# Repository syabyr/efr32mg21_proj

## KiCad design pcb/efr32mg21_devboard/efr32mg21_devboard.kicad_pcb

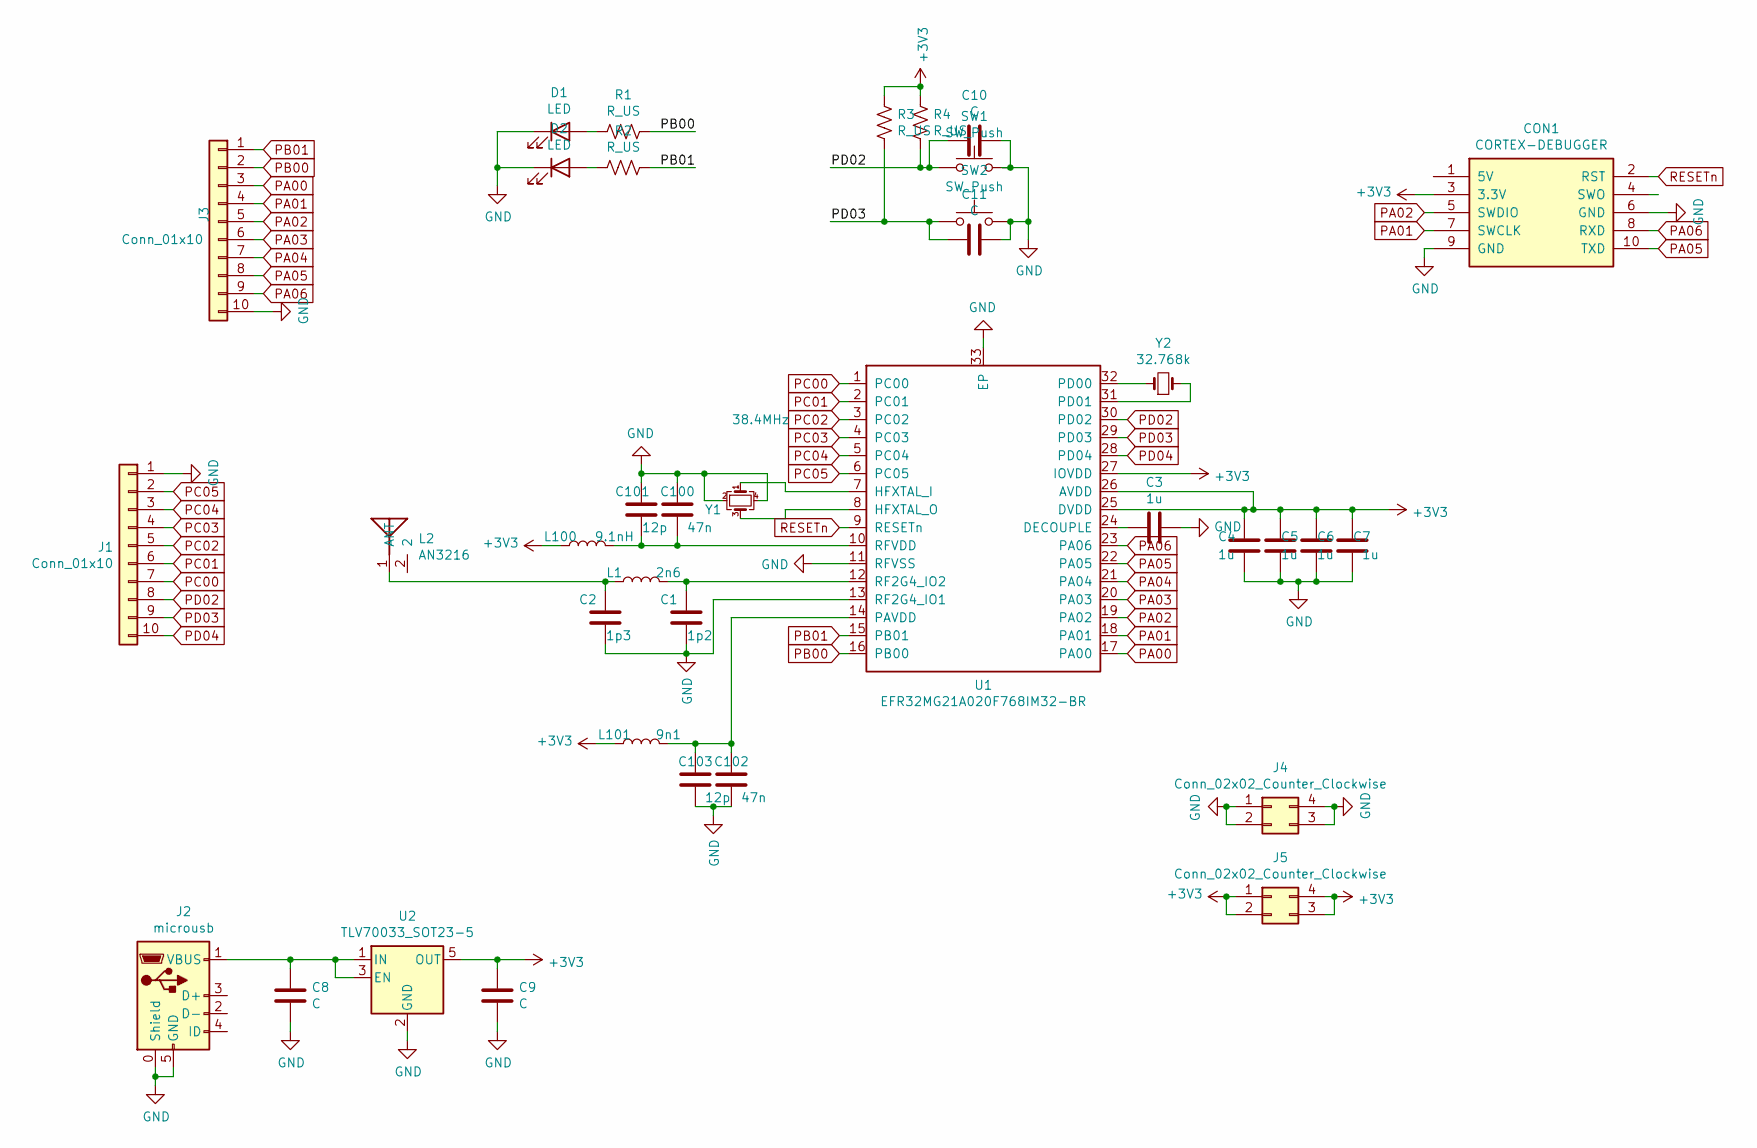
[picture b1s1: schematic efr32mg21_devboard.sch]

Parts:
C1: 1p2; C_0402_1005Metric
C2: 1p3; C_0402_1005Metric
C3, C4, C5, C6, C7: 1u; C_0402_1005Metric
C8, C9: C; C_1206_3216Metric
C10, C11: C; C_0603_1608Metric_Pad1.08x0.95mm_HandSolder
C100, C102: 47n; C_0402_1005Metric
C101, C103: 12p; C_0402_1005Metric
CON1: CORTEX-DEBUGGER; debugger_2x05_P1.27mm_Vertical
D1, D2: LED; LED_0805_2012Metric
J1, J3: Conn_01x10; PinHeader_1x10_P2.54mm_Vertical
J2: microusb; MICRO-USB_MICRO-USB-17
J4, J5: Conn_02x02_Counter_Clockwise; PinHeader_2x02_P2.54mm_Vertical
L1: 2n6; L_0402_1005Metric
L2: AN3216; ANT3216-2.4G
L100: 9.1nH; L_0603_1608Metric
L101: 9n1; L_0603_1608Metric
R1, R2, R3, R4: R_US; R_0603_1608Metric_Pad0.98x0.95mm_HandSolder
SW1, SW2: SW_Push; turtlekey
U1: EFR32MG21A020F768IM32-BR; QFN-32-1EP_4x4mm_P0.4mm_EP2.9x2.9mm
U2: TLV70033_SOT23-5; SOT-23-5
Y1: 38.4MHz; Crystal_SMD_3225-4Pin_3.2x2.5mm
Y2: 32.768k; Crystal_SMD_3215-2Pin_3.2x1.5mm

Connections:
+3V3: C4.2, C5.2, C6.2, C7.2, C9.1, CON1.3 (3.3V), J5.1, J5.2, J5.3, J5.4, L100.1, L101.1, R3.2, R4.2, U1.25 (DVDD), U1.26 (AVDD), U1.27 (IOVDD), U2.5 (OUT)
GND: C1.1, C2.1, C3.1, C4.1, C5.1, C6.1, C7.1, C8.2, C9.2, C10.1, C11.1, C100.2, C101.2, C102.1, C103.1, CON1.6 (GND), CON1.9 (GND), D1.1 (K), D2.1 (K), J1.1, J2.0 (Shield), J2.5 (GND), J3.10, J4.1, J4.2, J4.3, J4.4, SW1.2, SW2.2, U1.11 (RFVSS), U1.13 (RF2G4_IO1), U1.33 (EP), U2.2 (GND), Y1.2, Y1.4
unnamed: C1.2, L1.2, U1.12 (RF2G4_IO2)
unnamed: C2.2, L1.1, L2.1 (ANT)
unnamed: C3.2, U1.24 (DECOUPLE)
unnamed: C8.1, J2.1 (VBUS), U2.1 (IN), U2.3 (EN)
unnamed: C100.1, C101.1, L100.2, U1.10 (RFVDD)
unnamed: C102.2, C103.2, L101.2, U1.14 (PAVDD)
unnamed: D1.2 (A), R1.2
unnamed: D2.2 (A), R2.2
unnamed: U1.7 (HFXTAL_I), Y1.1
unnamed: U1.8 (HFXTAL_O), Y1.3
unnamed: U1.31 (PD01), Y2.2
unnamed: U1.32 (PD00), Y2.1
PA00: J3.3, U1.17 (PA00)
PA01: CON1.7 (SWCLK), J3.4, U1.18 (PA01)
PA02: CON1.5 (SWDIO), J3.5, U1.19 (PA02)
PA03: J3.6, U1.20 (PA03)
PA04: J3.7, U1.21 (PA04)
PA05: CON1.10 (TXD), J3.8, U1.22 (PA05)
PA06: CON1.8 (RXD), J3.9, U1.23 (PA06)
PB00: J3.2, R1.1, U1.16 (PB00)
PB01: J3.1, R2.1, U1.15 (PB01)
PC00: J1.7, U1.1 (PC00)
PC01: J1.6, U1.2 (PC01)
PC02: J1.5, U1.3 (PC02)
PC03: J1.4, U1.4 (PC03)
PC04: J1.3, U1.5 (PC04)
PC05: J1.2, U1.6 (PC05)
PD02: C10.2, J1.8, R4.1, SW1.1, U1.30 (PD02)
PD03: C11.2, J1.9, R3.1, SW2.1, U1.29 (PD03)
PD04: J1.10, U1.28 (PD04)
RESETn: CON1.2 (RST), U1.9 (RESETn)

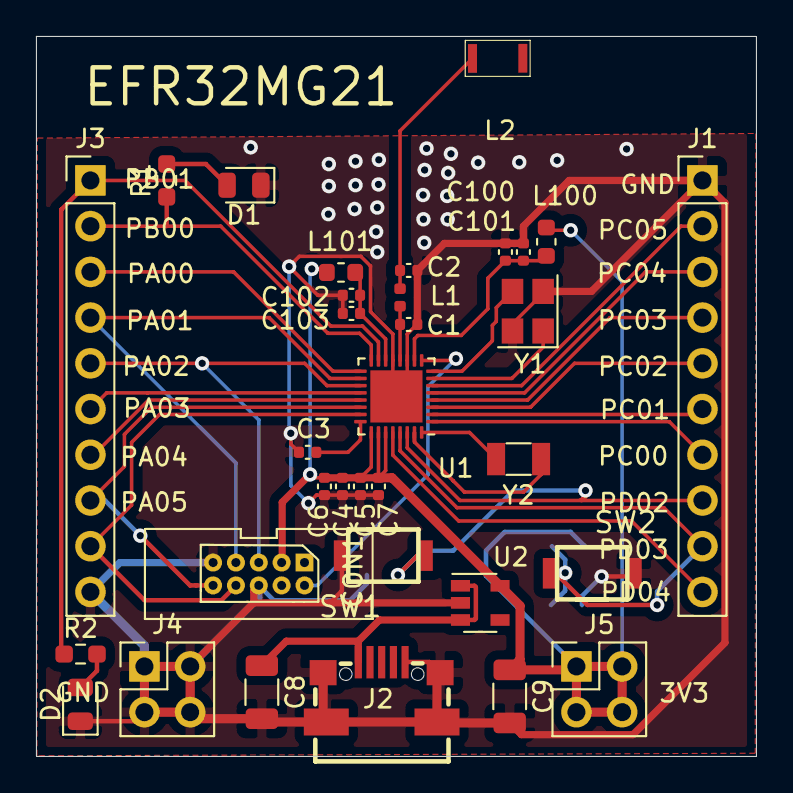
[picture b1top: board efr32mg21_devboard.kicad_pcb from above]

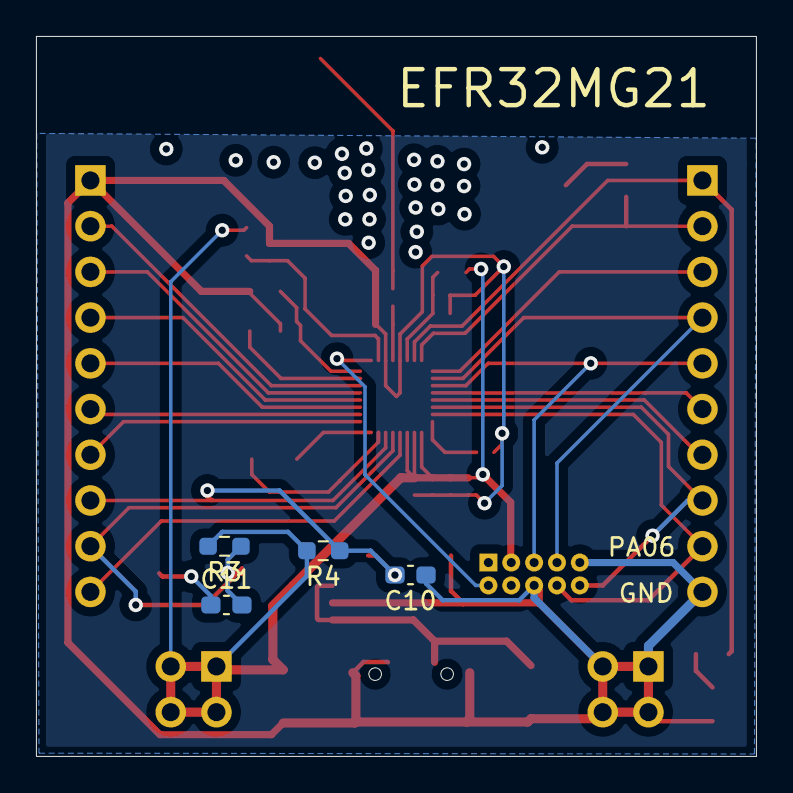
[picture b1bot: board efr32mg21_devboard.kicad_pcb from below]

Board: 2 copper layers, 40.0 x 40.0 mm, 37 parts (4 on the bottom side), 33 nets.

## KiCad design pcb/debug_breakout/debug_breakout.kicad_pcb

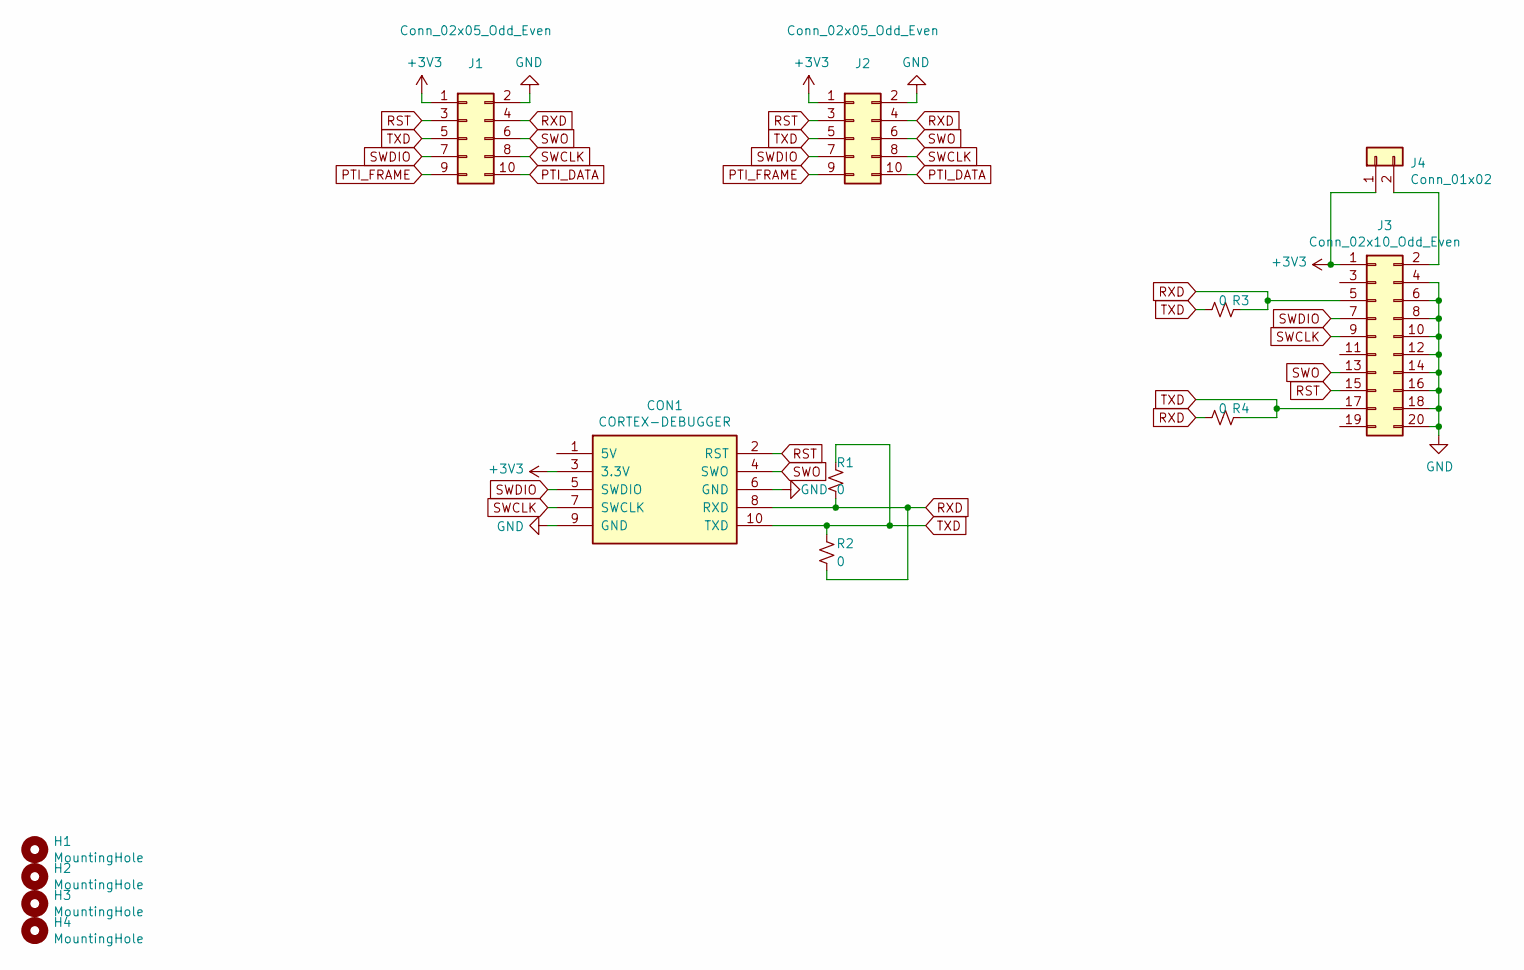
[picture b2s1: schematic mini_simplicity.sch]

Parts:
CON1: CORTEX-DEBUGGER; debugger_2x05_P1.27mm_Vertical
H1, H2, H3, H4: MountingHole; MountingHole_3.2mm_M3_ISO7380
J1: Conn_02x05_Odd_Even; debugger_2x05_P1.27mm_Vertical
J2: Conn_02x05_Odd_Even; PinHeader_2x05_P2.54mm_Vertical
J3: Conn_02x10_Odd_Even; PinHeader_2x10_P2.54mm_Vertical
J4: Conn_01x02; PinHeader_1x02_P2.54mm_Vertical
R1, R2, R3, R4: 0; R_0201_0603Metric

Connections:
+3V3: CON1.3 (3.3V), J1.1, J2.1, J3.1, J4.1
GND: CON1.6 (GND), CON1.9 (GND), J1.2, J2.2, J3.4, J3.6, J3.8, J3.10, J3.12, J3.14, J3.16, J3.18, J3.20
unnamed: J3.2, J4.2
PTI_DATA: J1.10, J2.10
PTI_FRAME: J1.9, J2.9
RST: CON1.2 (RST), J1.3, J2.3, J3.15
RXD: CON1.8 (RXD), J1.4, J2.4, J3.5, R1.2, R2.2, R3.1, R4.2
SWCLK: CON1.7 (SWCLK), J1.8, J2.8, J3.9
SWDIO: CON1.5 (SWDIO), J1.7, J2.7, J3.7
SWO: CON1.4 (SWO), J1.6, J2.6, J3.13
TXD: CON1.10 (TXD), J1.5, J2.5, J3.17, R1.1, R2.1, R3.2, R4.1

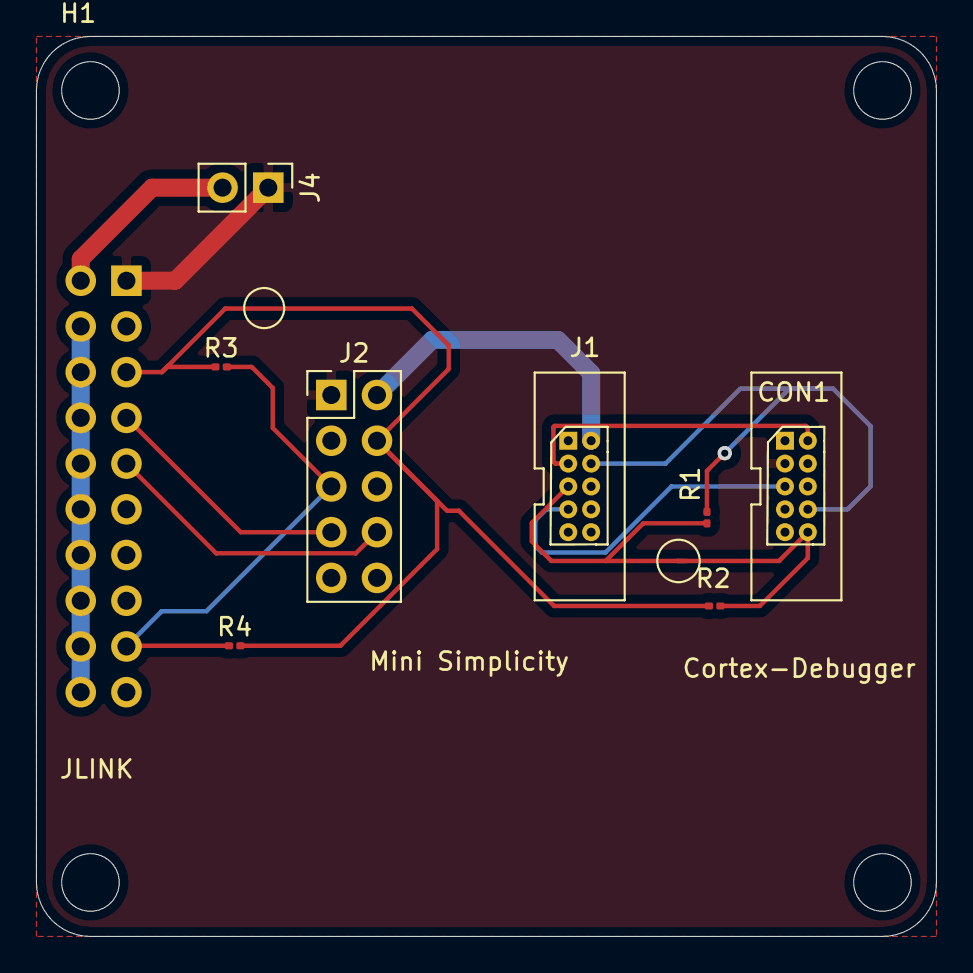
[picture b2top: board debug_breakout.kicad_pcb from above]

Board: 4 copper layers, 50.0 x 50.0 mm, 13 parts (1 on the bottom side), 11 nets.

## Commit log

2022-01-29 proj
2022-03-20 breakout board
2022-03-20 key touch
